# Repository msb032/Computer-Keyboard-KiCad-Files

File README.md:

# Computer-Keyboard-Files-STL-KiCad
KiCad files for a split custom computer keyboard design.
STL files for the case, plate, and keycaps for the keyboard design.

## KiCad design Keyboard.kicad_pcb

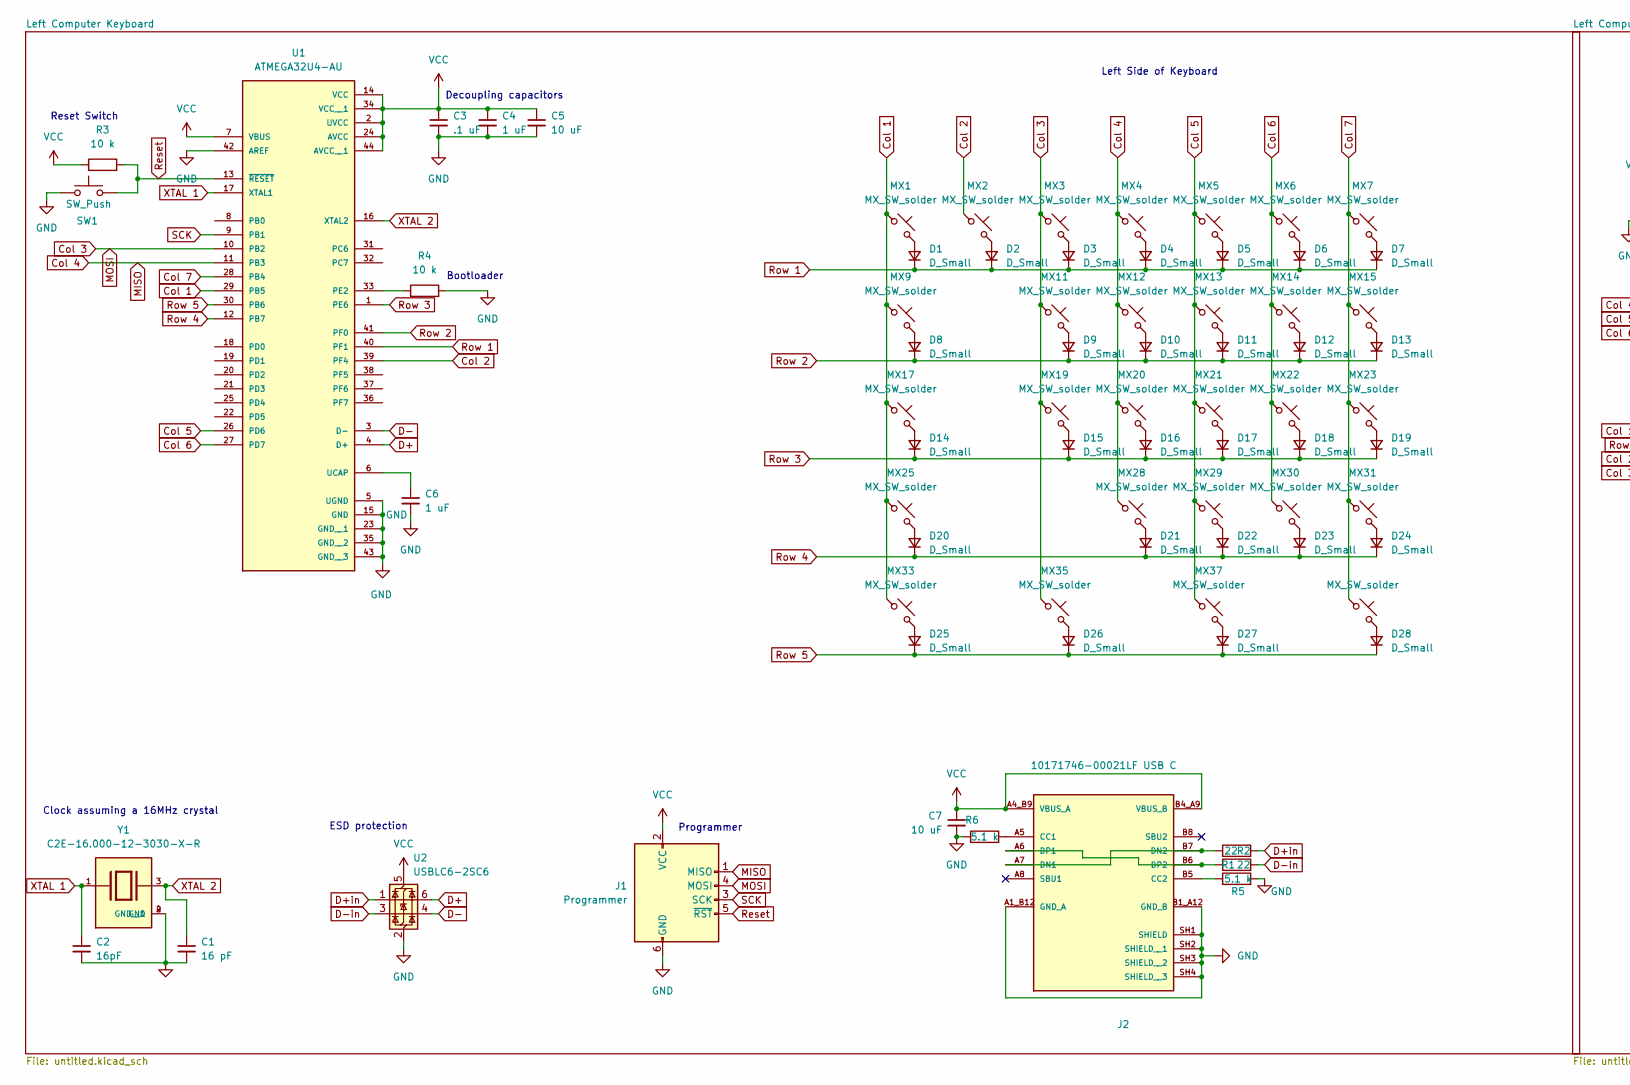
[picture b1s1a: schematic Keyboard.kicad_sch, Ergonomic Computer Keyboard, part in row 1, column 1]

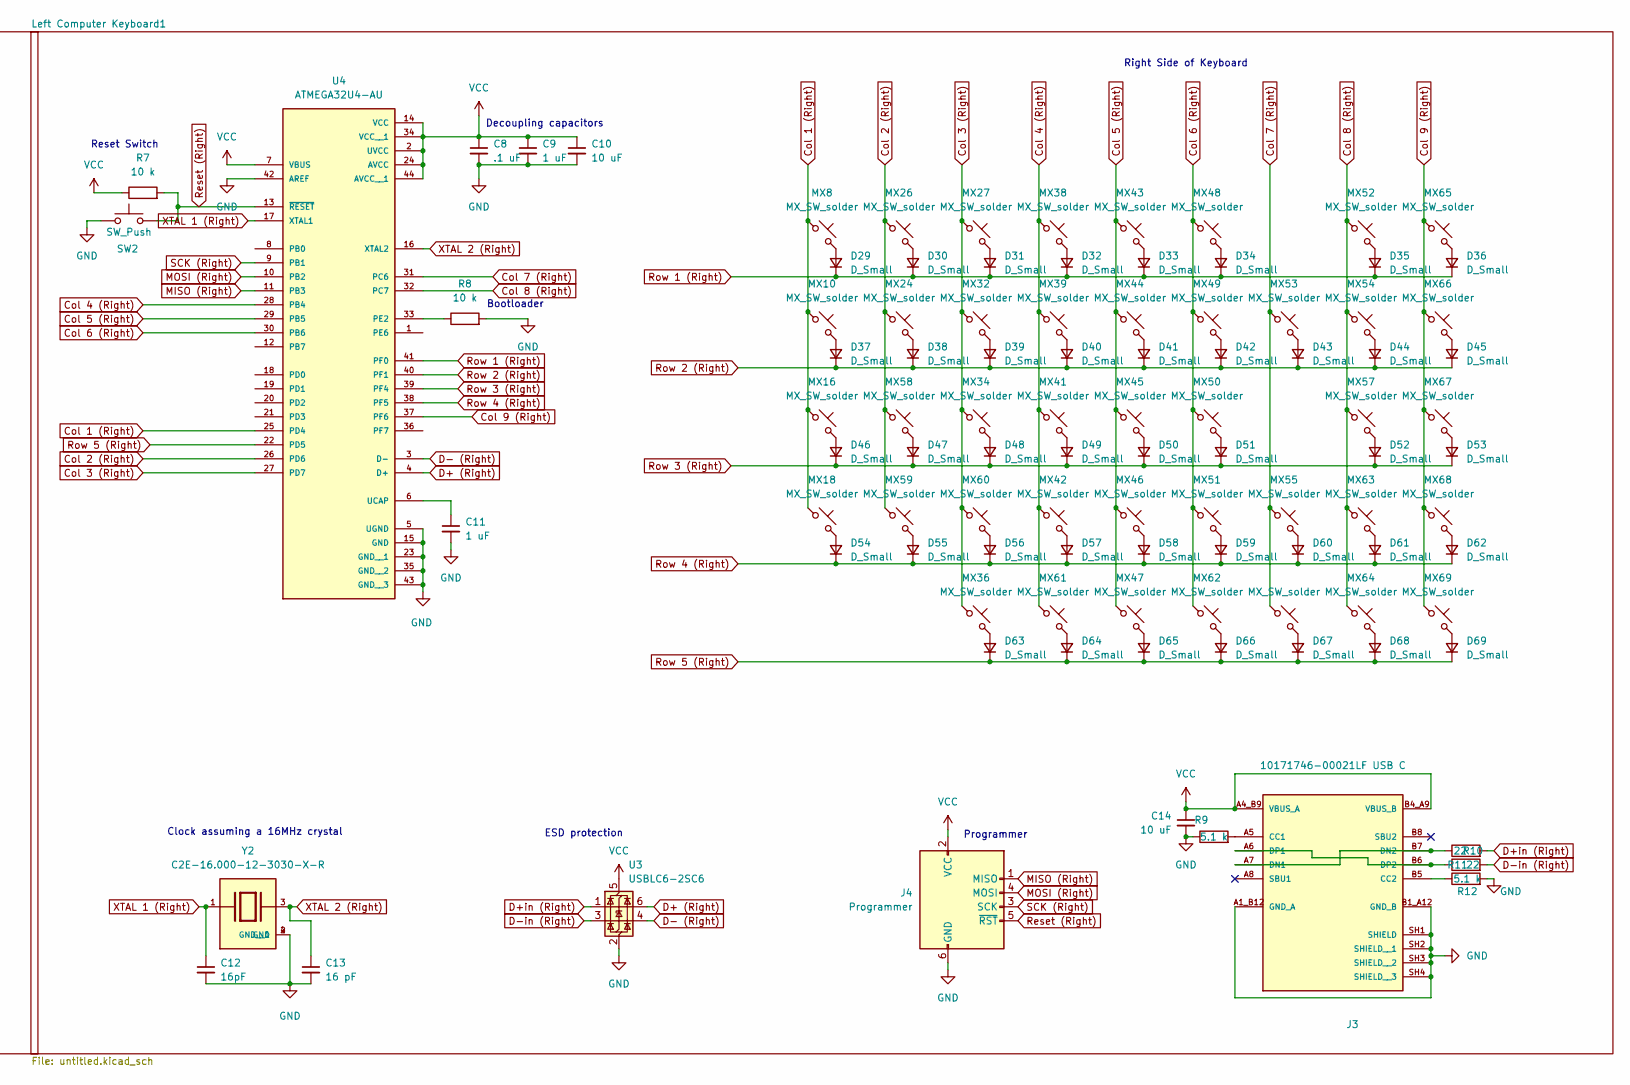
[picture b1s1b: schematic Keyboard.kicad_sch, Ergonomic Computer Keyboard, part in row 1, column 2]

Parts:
C1, C13: 16 pF; CAPC1608X90
C2, C12: 16pF; CAPC1608X90
C3, C8: .1 uF; CAPC1608X90
C4, C6, C9, C11: 1 uF; CAP_CC0603_YAG-M
C5, C7, C10, C14: 10 uF; C0603
D1, D2, D3, D4, D5, D6, D7, D8, D9, D10, D11, D12, D13, D14, D15, D16, D17, D18, D19, D20, D21, D22, D23, D24, D25, D26, D27, D28, D29, D30, D31, D32, D33, D34, D35, D36, D37, D38, D39, D40, D41, D42, D43, D44, D45, D46, D47, D48, D49, D50, D51, D52, D53, D54, D55, D56, D57, D58, D59, D60, D61, D62, D63, D64, D65, D66, D67, D68, D69: D_Small; CR_SOD323_MCC-M
J1, J4: Programmer; PinHeader_2x03_P2.54mm_Vertical
J2, J3: 10171746-00021LF USB C; AMPHENOL_10171746-00021LF; PARTREV A
MX1, MX2, MX3, MX4, MX5, MX6, MX7, MX8, MX9, MX10, MX11, MX12, MX13, MX14, MX15, MX16, MX17, MX18, MX19, MX20, MX21, MX22, MX23, MX24, MX25, MX26, MX27, MX28, MX29, MX30, MX31, MX32, MX33, MX34, MX35, MX36, MX37, MX38, MX39, MX40, MX41, MX42, MX43, MX44, MX45, MX46, MX47, MX48, MX49, MX50, MX51, MX52, MX53, MX54, MX55, MX56, MX57, MX58, MX59, MX60, MX61, MX62, MX63, MX64, MX65, MX66, MX67, MX68, MX69: MX_SW_solder; SW_MX_1u
R1, R2, R10, R11: 22; R0402
R3, R4, R7, R8: 10 k; RESC1607X60N
R5, R6, R9, R12: 5.1 k; RESC1607X60N
SW1, SW2: SW_Push; SW_TS18-5-17-SL-160-SMT-TR
U1, U4: ATMEGA32U4-AU; QFP80P1200X1200X120-44N
U2, U3: USBLC6-2SC6; SOT-23-6
Y1, Y2: C2E-16.000-12-3030-X-R; XTAL_C2E-16.000-12-3030-X-R; PARTREV August 01, 2022

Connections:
Col 1: MX1.1, MX9.1, MX17.1, MX25.1, MX33.1, U1.29 (PB5)
Col 1 (Right): MX8.1, MX10.1, MX16.1, MX18.1, U4.25 (PD4)
Col 2: MX2.1, U1.39 (PF4)
Col 2 (Right): MX24.1, MX26.1, MX58.1, MX59.1, U4.26 (PD6)
Col 3: J1.4 (MOSI), MX3.1, MX11.1, MX19.1, MX35.1, U1.10 (PB2)
Col 3 (Right): MX27.1, MX32.1, MX34.1, MX36.1, MX60.1, U4.27 (PD7)
Col 4: J1.1 (MISO), MX4.1, MX12.1, MX20.1, MX28.1, U1.11 (PB3)
Col 4 (Right): MX38.1, MX39.1, MX41.1, MX42.1, MX61.1, U4.28 (PB4)
Col 5: MX5.1, MX13.1, MX21.1, MX29.1, MX37.1, U1.26 (PD6)
Col 5 (Right): MX43.1, MX44.1, MX45.1, MX46.1, MX47.1, U4.29 (PB5)
Col 6: MX6.1, MX14.1, MX22.1, MX30.1, U1.27 (PD7)
Col 6 (Right): MX48.1, MX49.1, MX50.1, MX51.1, MX62.1, U4.30 (PB6)
Col 7: MX7.1, MX15.1, MX23.1, MX31.1, MX40.1, U1.28 (PB4)
Col 7 (Right): MX53.1, MX55.1, MX56.1, U4.31 (PC6)
Col 8 (Right): MX52.1, MX54.1, MX57.1, MX63.1, MX64.1, U4.32 (PC7)
Col 9 (Right): MX65.1, MX66.1, MX67.1, MX68.1, MX69.1, U4.37 (PF6)
D+: U1.4 (D+), U2.6 (I/O1)
D+ (Right): U3.6 (I/O1), U4.4 (D+)
D+in: R2.2, U2.1 (I/O1)
D+in (Right): R10.2, U3.1 (I/O1)
D-: U1.3 (D-), U2.4 (I/O2)
D- (Right): U3.4 (I/O2), U4.3 (D-)
D-in: R1.2, U2.3 (I/O2)
D-in (Right): R11.2, U3.3 (I/O2); also elsewhere on the board
GND: C1.2, C2.2, C3.2, C4.2, C5.2, C6.2, C7.2, C8.2, C9.2, C10.2, C11.2, C12.2, C13.2, C14.2, J1.6 (GND), J2.A1_B12 (GND_A), J2.B1_A12 (GND_B), J2.SH1 (SHIELD), J2.SH2 (SHIELD__1), J2.SH3 (SHIELD__2), J2.SH4 (SHIELD__3), J3.A1_B12 (GND_A), J3.B1_A12 (GND_B), J3.SH1 (SHIELD), J3.SH2 (SHIELD__1), J3.SH3 (SHIELD__2), J3.SH4 (SHIELD__3), J4.6 (GND), R4.2, R5.2, R6.1, R8.2, R9.1, R12.2, SW1.1, SW2.1, U1.5 (UGND), U1.15 (GND), U1.23 (GND__1), U1.35 (GND__2), U1.42 (AREF), U1.43 (GND__3), U2.2 (GND), U3.2 (GND), U4.5 (UGND), U4.15 (GND), U4.23 (GND__1), U4.35 (GND__2), U4.42 (AREF), U4.43 (GND__3), Y1.2 (GND), Y1.4 (GND__1), Y2.2 (GND), Y2.4 (GND__1); also elsewhere on the board
MISO (Right): J4.1 (MISO), U4.11 (PB3)
MOSI (Right): J4.4 (MOSI), U4.10 (PB2)
unnamed: D1.2 (A), MX1.2
unnamed: D2.2 (A), MX2.2
unnamed: D3.2 (A), MX3.2
unnamed: D4.2 (A), MX4.2
unnamed: D5.2 (A), MX5.2
unnamed: D6.2 (A), MX6.2
unnamed: D7.2 (A), MX7.2
unnamed: D8.2 (A), MX9.2
unnamed: D9.2 (A), MX11.2
unnamed: D10.2 (A), MX12.2
unnamed: D11.2 (A), MX13.2
unnamed: D12.2 (A), MX14.2
unnamed: D13.2 (A), MX15.2
unnamed: D14.2 (A), MX17.2
unnamed: D15.2 (A), MX19.2
unnamed: D16.2 (A), MX20.2
unnamed: D17.2 (A), MX21.2
unnamed: D18.2 (A), MX22.2
unnamed: D19.2 (A), MX23.2
unnamed: D20.2 (A), MX25.2
unnamed: D21.2 (A), MX28.2
unnamed: D22.2 (A), MX29.2
unnamed: D23.2 (A), MX30.2
unnamed: D24.2 (A), MX31.2
unnamed: D25.2 (A), MX33.2
unnamed: D26.2 (A), MX35.2
unnamed: D27.2 (A), MX37.2
unnamed: D28.2 (A), MX40.2
unnamed: D29.2 (A), MX8.2
unnamed: D30.2 (A), MX26.2
unnamed: D31.2 (A), MX27.2
unnamed: D32.2 (A), MX38.2
unnamed: D33.2 (A), MX43.2
unnamed: D34.2 (A), MX48.2
unnamed: D35.2 (A), MX52.2
unnamed: D36.2 (A), MX65.2
unnamed: D37.2 (A), MX10.2
unnamed: D38.2 (A), MX24.2
unnamed: D39.2 (A), MX32.2
unnamed: D40.2 (A), MX39.2
unnamed: D41.2 (A), MX44.2
unnamed: D42.2 (A), MX49.2
unnamed: D43.2 (A), MX53.2
unnamed: D44.2 (A), MX54.2
unnamed: D45.2 (A), MX66.2
unnamed: D46.2 (A), MX16.2
unnamed: D47.2 (A), MX58.2
unnamed: D48.2 (A), MX34.2
unnamed: D49.2 (A), MX41.2
unnamed: D50.2 (A), MX45.2
unnamed: D51.2 (A), MX50.2
unnamed: D52.2 (A), MX57.2
unnamed: D53.2 (A), MX67.2
unnamed: D54.2 (A), MX18.2
unnamed: D55.2 (A), MX59.2
unnamed: D56.2 (A), MX60.2
unnamed: D57.2 (A), MX42.2
unnamed: D58.2 (A), MX46.2
unnamed: D59.2 (A), MX51.2
unnamed: D60.2 (A), MX55.2
unnamed: D61.2 (A), MX63.2
unnamed: D62.2 (A), MX68.2
unnamed: D63.2 (A), MX36.2
unnamed: D64.2 (A), MX61.2
unnamed: D65.2 (A), MX47.2
unnamed: D66.2 (A), MX62.2
unnamed: D67.2 (A), MX56.2
unnamed: D68.2 (A), MX64.2
unnamed: D69.2 (A), MX69.2
unnamed: J2.A5 (CC1), R6.2
unnamed: J2.B5 (CC2), R5.1
unnamed: J2.A7 (DN1), J2.B7 (DN2), R2.1
unnamed: J2.A6 (DP1), J2.B6 (DP2), R1.1
unnamed: J3.A5 (CC1), R9.2
unnamed: J3.B5 (CC2), R12.1
unnamed: J3.A7 (DN1), J3.B7 (DN2), R10.1
unnamed 103: J3.A6 (DP1), J3.B6 (DP2), R11.1; also elsewhere on the board
unnamed: R4.1, U1.33 (PE2)
unnamed 105: C6.1, U1.6 (UCAP); also elsewhere on the board
unnamed: R8.1, U4.33 (PE2)
unnamed: C11.1, U4.6 (UCAP)
Reset: J1.5 (~RST), R3.2, SW1.2, U1.13 (~RESET); also elsewhere on the board
Reset (Right): J4.5 (~RST), R7.2, SW2.2, U4.13 (~RESET); also elsewhere on the board
Row 1: D1.1 (K), D2.1 (K), D3.1 (K), D4.1 (K), D5.1 (K), D6.1 (K), D7.1 (K), U1.40 (PF1)
Row 1 (Right): D29.1 (K), D30.1 (K), D31.1 (K), D32.1 (K), D33.1 (K), D34.1 (K), D35.1 (K), D36.1 (K), U4.41 (PF0)
Row 2: D8.1 (K), D9.1 (K), D10.1 (K), D11.1 (K), D12.1 (K), D13.1 (K), U1.41 (PF0)
Row 2 (Right): D37.1 (K), D38.1 (K), D39.1 (K), D40.1 (K), D41.1 (K), D42.1 (K), D43.1 (K), D44.1 (K), D45.1 (K), U4.40 (PF1)
Row 3: D14.1 (K), D15.1 (K), D16.1 (K), D17.1 (K), D18.1 (K), D19.1 (K), U1.1 (PE6)
Row 3 (Right): D46.1 (K), D47.1 (K), D48.1 (K), D49.1 (K), D50.1 (K), D51.1 (K), D52.1 (K), D53.1 (K), U4.39 (PF4)
Row 4: D20.1 (K), D21.1 (K), D22.1 (K), D23.1 (K), D24.1 (K), U1.12 (PB7)
Row 4 (Right): D54.1 (K), D55.1 (K), D56.1 (K), D57.1 (K), D58.1 (K), D59.1 (K), D60.1 (K), D61.1 (K), D62.1 (K), U4.38 (PF5)
Row 5: D25.1 (K), D26.1 (K), D27.1 (K), D28.1 (K), U1.30 (PB6)
Row 5 (Right): D63.1 (K), D64.1 (K), D65.1 (K), D66.1 (K), D67.1 (K), D68.1 (K), D69.1 (K), U4.22 (PD5)
SCK: J1.3 (SCK), U1.9 (PB1)
SCK (Right): J4.3 (SCK), U4.9 (PB1)
VCC: C3.1, C4.1, C5.1, C7.1, C8.1, C9.1, C10.1, C14.1, J1.2 (VCC), J2.A4_B9 (VBUS_A), J2.B4_A9 (VBUS_B), J3.A4_B9 (VBUS_A), J3.B4_A9 (VBUS_B), J4.2 (VCC), R3.1, R7.1, U1.2 (UVCC), U1.7 (VBUS), U1.14 (VCC), U1.24 (AVCC), U1.34 (VCC__1), U1.44 (AVCC__1), U2.5 (VBUS), U3.5 (VBUS), U4.2 (UVCC), U4.7 (VBUS), U4.14 (VCC), U4.24 (AVCC), U4.34 (VCC__1), U4.44 (AVCC__1); also elsewhere on the board
XTAL 1: C2.1, U1.17 (XTAL1), Y1.1
XTAL 1 (Right): C12.1, U4.17 (XTAL1), Y2.1
XTAL 2: C1.1, U1.16 (XTAL2), Y1.3; also elsewhere on the board
XTAL 2 (Right): C13.1, U4.16 (XTAL2), Y2.3

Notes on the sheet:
Decoupling capacitors
Right Side of Keyboard
Left Side of Keyboard
Reset Switch
ESD protection
Bootloader
Programmer
Clock assuming a 16MHz crystal

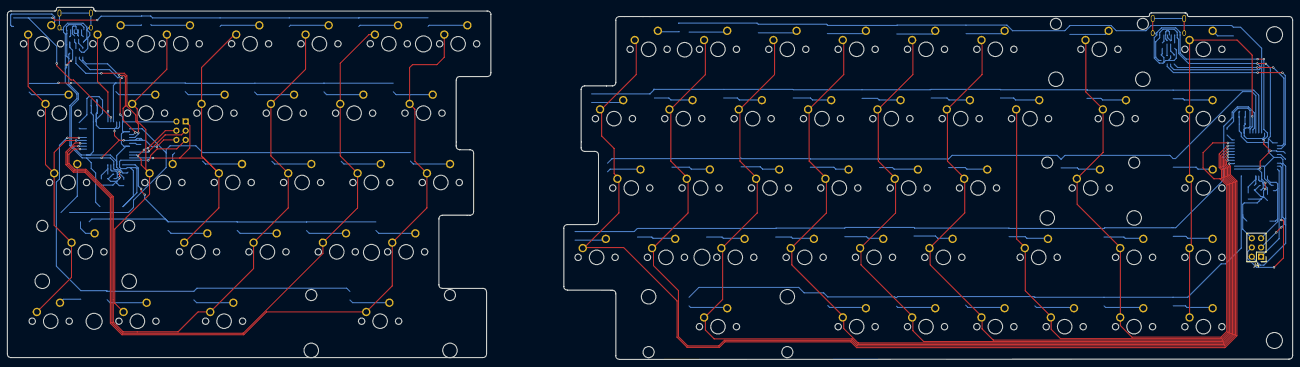
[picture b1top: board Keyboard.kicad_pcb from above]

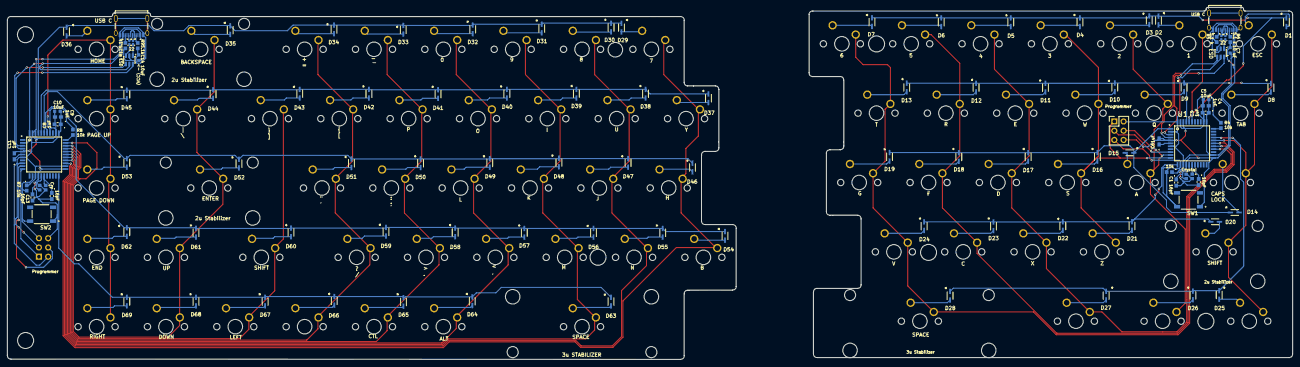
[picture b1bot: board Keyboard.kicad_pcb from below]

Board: 2 copper layers, 353.1 x 96.7 mm, 176 parts (106 on the bottom side), 127 nets.

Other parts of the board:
10k: 10 k; RESC1607X60N
22: 22; R0402
C1 16pF: 16 pF; CAPC1608X90
C14 10uF: 10 uF; C0603
C61uF: 1 uF; CAP_CC0603_YAG-M
R7 10k: 10 k; RESC1607X60N

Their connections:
D-in (Right): 22.2; also elsewhere on the board
GND: C1 16pF.2, C14 10uF.2, C61uF.2; also elsewhere on the board
unnamed 103: 22.1; also elsewhere on the board
unnamed 105: C61uF.1; also elsewhere on the board
Reset: 10k.2; also elsewhere on the board
Reset (Right): R7 10k.2; also elsewhere on the board
VCC: 10k.1, C14 10uF.1, R7 10k.1; also elsewhere on the board
XTAL 2: C1 16pF.1; also elsewhere on the board

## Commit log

2025-12-02 Rename project and include STL file details
    Updated project title and added STL file information.
